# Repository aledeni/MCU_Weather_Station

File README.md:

# MCU Weather Station

The heart of the board is the ATmega328P microcontroller, it also features a 6-pin AVR-ISP connector for burning the bootloader and a USB connector with serial driver for programming the microcontroller. For connectivity, an ESP8266 Wi-Fi module is provided, connected to the ATmega328P.
The boards were ordered from China via the JLCPCB website (5 pcs at a cost of 31 EUR) and the components will be assembled and soldered by myself.
The board schematic can be found in schematic/MCU_Weather_Station.pdf from this git repository.

__Why this board?__

The purpose of the board is to provide a simple but practical example of an online weather station that will use the api.open-meteo.com server for web requests, weather information such as temperature, humidity and time zone will be shown on the OLED display. I will develop the firmware using Arduino IDE.

__PCB view:__

__3D view:__

__Components:__

- 1x ATmega328P DIP-28
- 1x CH340C serial driver SMD
- 1x ESP8266 Olimex_MOD-WIFI-ESP8266-DEV module
- 1x OLED 128x64 SSD1306 display
- 1x AMS1117 voltage regulator (from 5V to 3.3V)
- 1x USB-B THT connector
- 1x DC Barrel Jack 5V THT
- 1x 16 MHz crystal
- 1x 5mm blue LED
- 1x 5mm green LED
- 1x SMD red power LED
- 2x 6mm THT push buttons
- 1x 2x3 AVR-ISP header
- 7x Resistors THT (3x 220Ω | 2x 10kΩ | 1x 1kΩ | 1x 2kΩ)
- 8x 100nF (0.1uF) ceramic capacitors THT
- 2x 22pF ceramic capacitors THT
- 3x 10uF electrolytic radial capacitors THT

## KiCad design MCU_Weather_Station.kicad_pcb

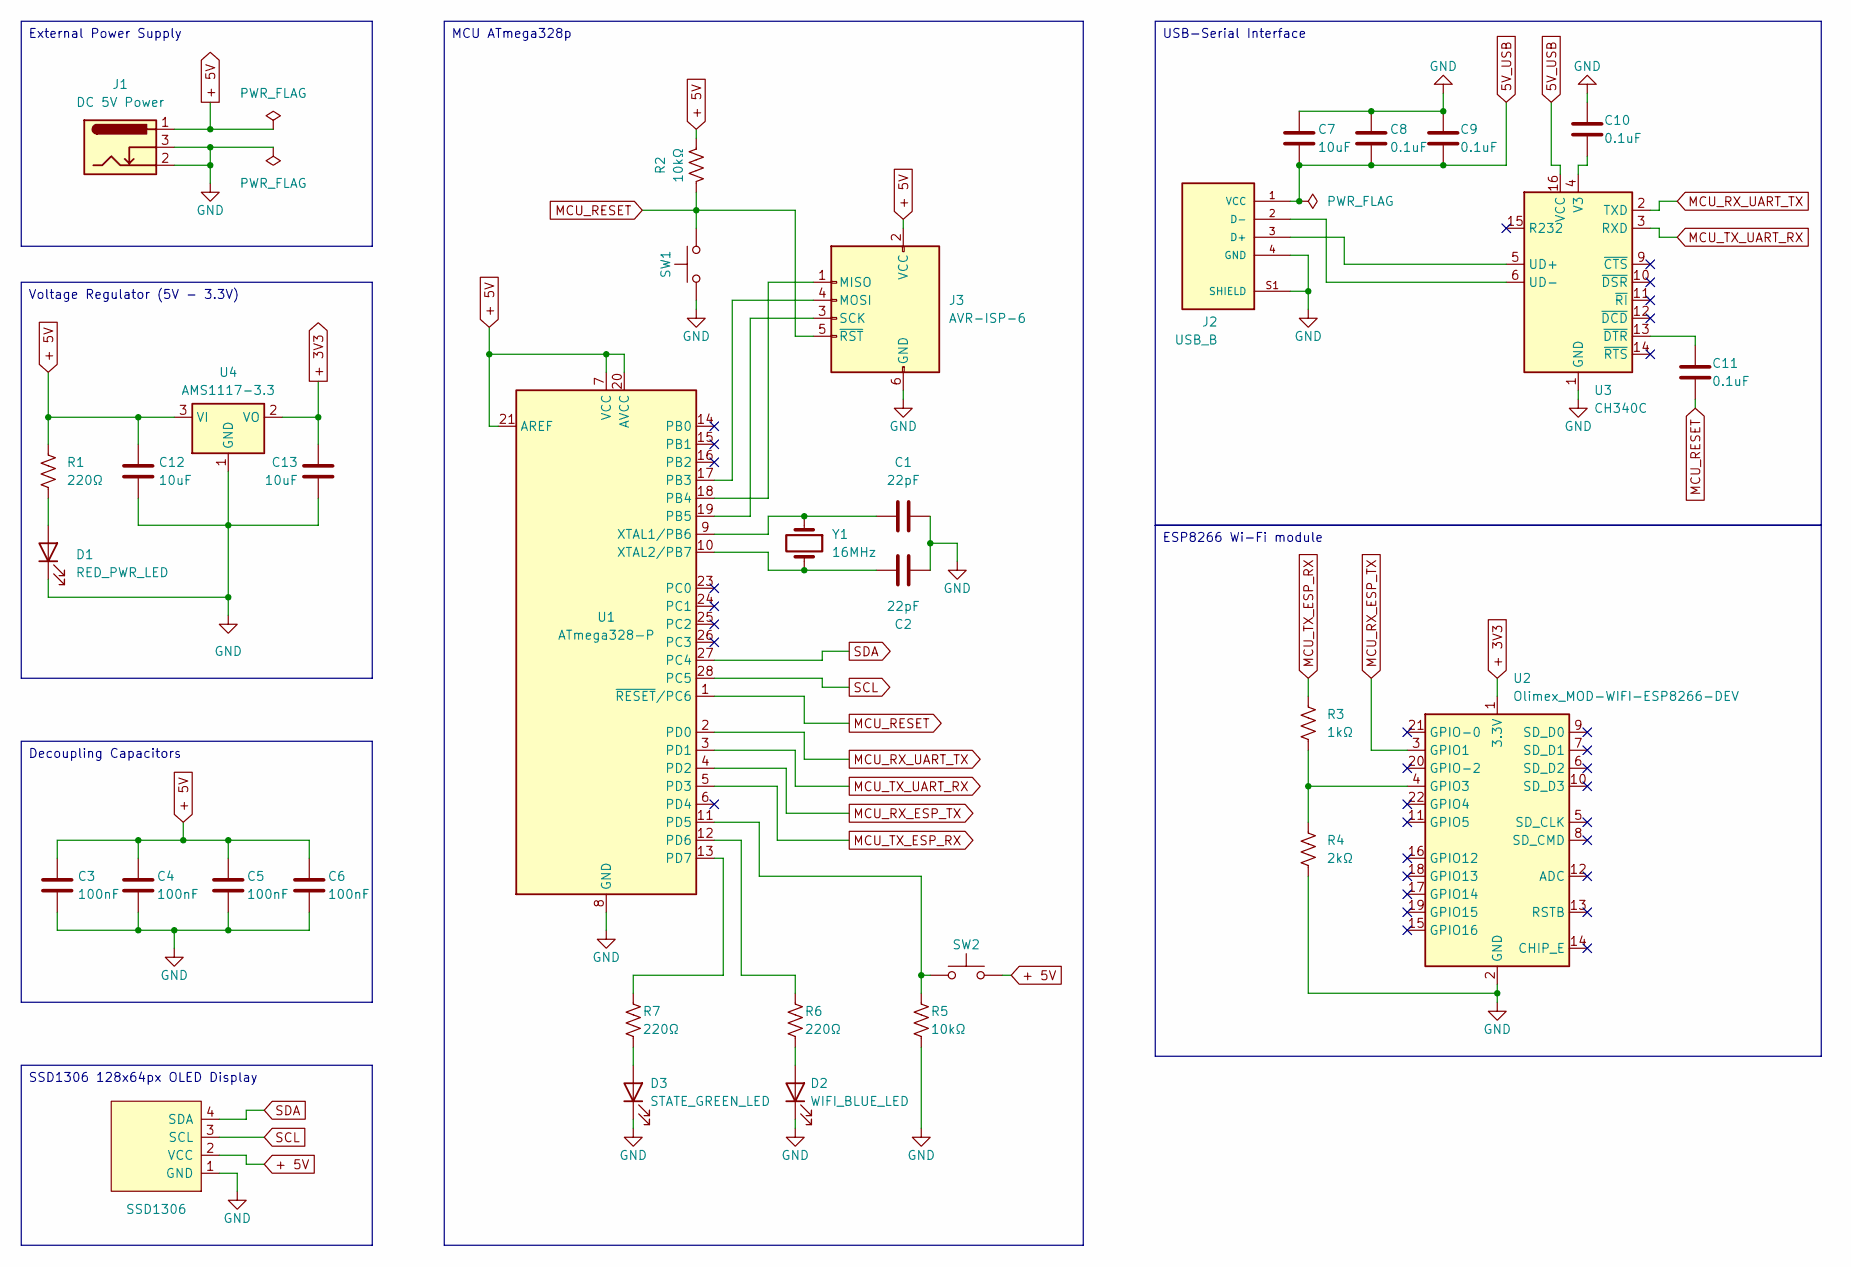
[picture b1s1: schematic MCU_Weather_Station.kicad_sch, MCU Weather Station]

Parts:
Brd1: SSD1306; 128x64OLED
C1, C2: 22pF; C_Disc_D3.0mm_W2.0mm_P2.50mm
C3, C4, C5, C6: 100nF; C_Disc_D5.0mm_W2.5mm_P5.00mm
C7, C12, C13: 10uF; CP_Radial_D5.0mm_P2.00mm
C8, C9, C10, C11: 0.1uF; C_Disc_D5.0mm_W2.5mm_P5.00mm
D1: RED_PWR_LED; LED_1206_3216Metric
D2: WIFI_BLUE_LED; LED_D5.0mm
D3: STATE_GREEN_LED; LED_D5.0mm
J1: DC 5V Power; BarrelJack_Horizontal
J2: USB_B; SAMTEC_USB-B-S-X-X-TH; PARTREV Q
J3: AVR-ISP-6; PinHeader_2x03_P2.54mm_Vertical
R1, R6, R7: 220Ω; R_Axial_DIN0207_L6.3mm_D2.5mm_P7.62mm_Horizontal
R2, R5: 10kΩ; R_Axial_DIN0207_L6.3mm_D2.5mm_P7.62mm_Horizontal
R3: 1kΩ; R_Axial_DIN0207_L6.3mm_D2.5mm_P7.62mm_Horizontal
R4: 2kΩ; R_Axial_DIN0207_L6.3mm_D2.5mm_P7.62mm_Horizontal
SW1: MCU_RESET_BUTTON; SW_PUSH_6mm
SW2: SW_Push; SW_PUSH_6mm
U1: ATmega328-P; DIP-28_W7.62mm
U2: Olimex_MOD-WIFI-ESP8266-DEV
U3: CH340C; SOIC-16_3.9x9.9mm_P1.27mm
U4: AMS1117-3.3; SOT-223-3_TabPin2
Y1: 16MHz; Crystal_HC49-4H_Vertical

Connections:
5V_USB: C7.2, C8.2, C9.2, J2.1 (VCC), U3.16 (VCC)
+ 3V3: C13.1, U2.1 (3.3V), U4.2 (VO)
+ 5V: Brd1.2 (VCC), C3.2, C4.2, C5.2, C6.2, C12.1, J1.1, J3.2 (VCC), R1.1, R2.2, SW2.2, U1.7 (VCC), U1.20 (AVCC), U1.21 (AREF), U4.3 (VI)
GND: Brd1.1 (GND), C1.2, C2.2, C3.1, C4.1, C5.1, C6.1, C7.1, C8.1, C9.1, C10.1, C12.2, C13.2, D1.1 (K), D2.1 (K), D3.1 (K), J1.2, J1.3, J2.4 (GND), J2.S1 (SHIELD), J2.S2 (SHIELD), J3.6 (GND), R4.2, R5.1, SW1.1, U1.8 (GND), U1.22 (GND), U2.2 (GND), U3.1 (GND), U4.1 (GND)
MCU_RESET: C11.2, J3.5 (~RST), R2.1, SW1.2, U1.1 (~RESET/PC6)
MCU_RX_ESP_TX: U1.4 (PD2), U2.3 (GPIO1)
MCU_RX_UART_TX: U1.2 (PD0), U3.2 (TXD)
MCU_TX_ESP_RX: R3.1, U1.5 (PD3)
MCU_TX_UART_RX: U1.3 (PD1), U3.3 (RXD)
unnamed: D1.2 (A), R1.2
unnamed: D2.2 (A), R6.1
unnamed: D3.2 (A), R7.1
unnamed: J2.3 (D+), U3.5 (UD+)
unnamed: J2.2 (D-), U3.6 (UD-)
unnamed: J3.1 (MISO), U1.18 (PB4)
unnamed: J3.4 (MOSI), U1.17 (PB3)
unnamed: J3.3 (SCK), U1.19 (PB5)
unnamed: R5.2, SW2.1, U1.11 (PD5)
unnamed: R6.2, U1.12 (PD6)
unnamed: R7.2, U1.13 (PD7)
unnamed: C1.1, U1.9 (XTAL1/PB6), Y1.1
unnamed: C2.1, U1.10 (XTAL2/PB7), Y1.2
unnamed: R3.2, R4.1, U2.4 (GPIO3)
unnamed: C10.2, U3.4 (V3)
unnamed: C11.1, U3.13 (~DTR)
SCL: Brd1.3 (SCL), U1.28 (PC5)
SDA: Brd1.4 (SDA), U1.27 (PC4)

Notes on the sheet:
Decoupling Capacitors
USB-Serial Interface
MCU ATmega328p
SSD1306 128x64px OLED Display
ESP8266 Wi-Fi module
External Power Supply
Voltage Regulator (5V - 3.3V)

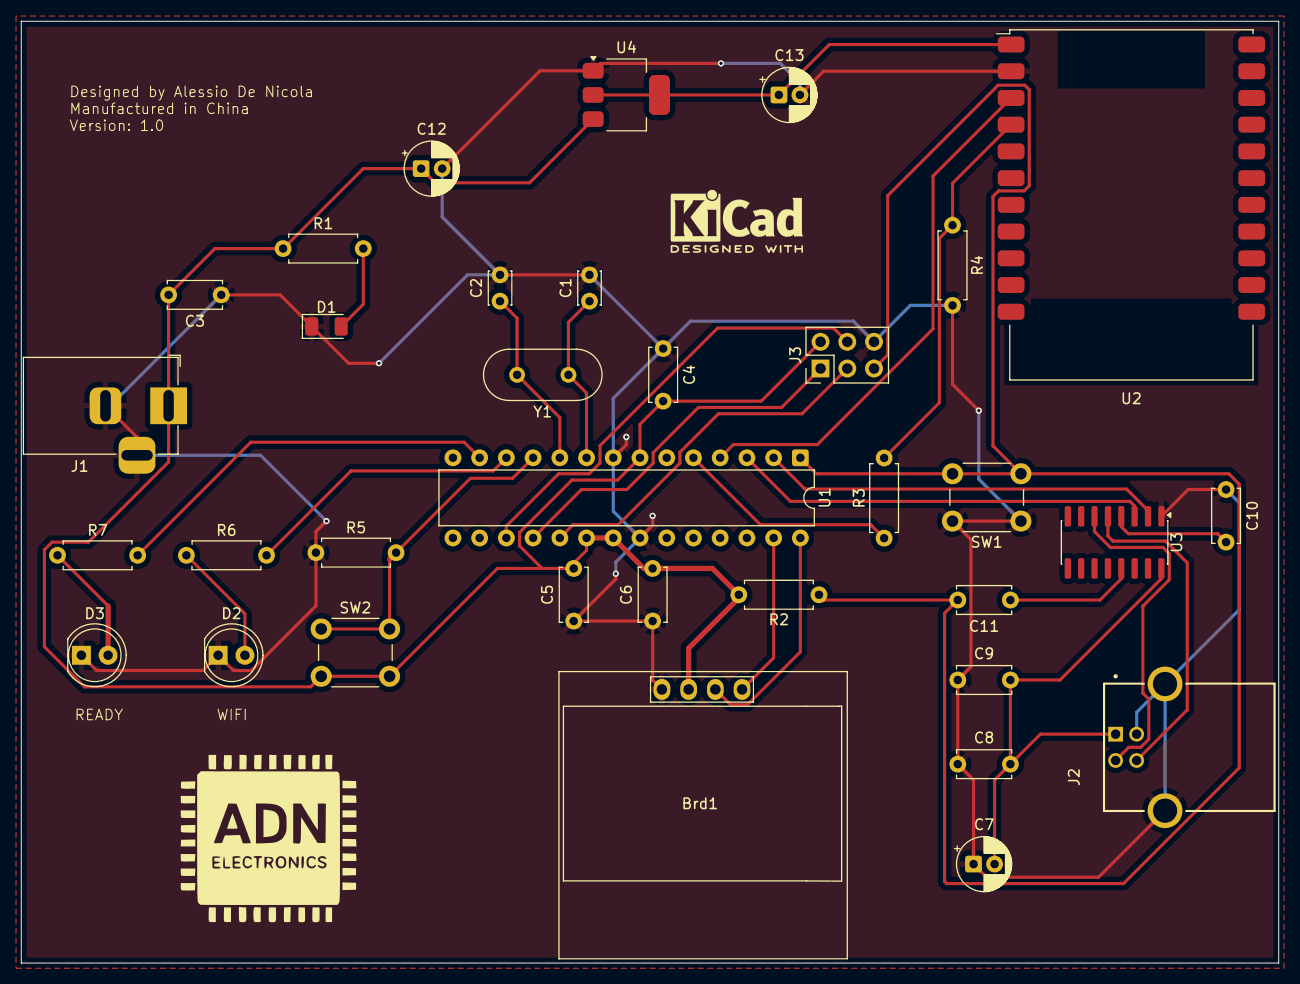
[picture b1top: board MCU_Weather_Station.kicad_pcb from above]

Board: 2 copper layers, 119.5 x 89.5 mm, 34 parts (0 on the bottom side), 27 nets.

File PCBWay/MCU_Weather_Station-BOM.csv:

"Id";"Designator";"Footprint";"Quantity";"Designation";"Supplier and ref";
1;"C6,C3,C5,C4";"C_Disc_D5.0mm_W2.5mm_P5.00mm";4;"100nF";;;
2;"C10,C11,C8,C9";"C_Disc_D5.0mm_W2.5mm_P5.00mm";4;"0.1uF";;;
3;"SW1";"SW_PUSH_6mm";1;"MCU_RESET_BUTTON";;;
4;"J3";"PinHeader_2x03_P2.54mm_Vertical";1;"AVR-ISP-6";;;
5;"D2";"LED_D5.0mm";1;"WIFI_BLUE_LED";;;
6;"U3";"SOIC-16_3.9x9.9mm_P1.27mm";1;"CH340C";;;
7;"R7,R1,R6";"R_Axial_DIN0207_L6.3mm_D2.5mm_P7.62mm_Horizontal";3;"220Ω";;;
8;"C13,C7,C12";"CP_Radial_D5.0mm_P2.00mm";3;"10uF";;;
9;"U2";"Olimex_MOD-WIFI-ESP8266-DEV";1;"Olimex_MOD-WIFI-ESP8266-DEV";;;
10;"R2,R5";"R_Axial_DIN0207_L6.3mm_D2.5mm_P7.62mm_Horizontal";2;"10kΩ";;;
11;"U1";"DIP-28_W7.62mm";1;"ATmega328-P";;;
12;"D3";"LED_D5.0mm";1;"STATE_GREEN_LED";;;
13;"J2";"SAMTEC_USB-B-S-X-X-TH";1;"USB_B";;;
14;"Y1";"Crystal_HC49-4H_Vertical";1;"16MHz";;;
15;"Brd1";"128x64OLED";1;"SSD1306";;;
16;"R3";"R_Axial_DIN0207_L6.3mm_D2.5mm_P7.62mm_Horizontal";1;"1kΩ";;;
17;"C2,C1";"C_Disc_D3.0mm_W2.0mm_P2.50mm";2;"22pF";;;
18;"R4";"R_Axial_DIN0207_L6.3mm_D2.5mm_P7.62mm_Horizontal";1;"2kΩ";;;
19;"SW2";"SW_PUSH_6mm";1;"SW_Push";;;
20;"J1";"BarrelJack_Horizontal";1;"DC 5V Power";;;
21;"D1";"LED_1206_3216Metric";1;"RED_PWR_LED";;;
22;"U4";"SOT-223-3_TabPin2";1;"AMS1117-3.3";;;

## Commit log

2026-02-28 Remove backups folder from tracking
2026-02-28 Add filled zones (GND front and bottom layer) and resolve all DRC errors
2026-02-28 Add PCBWay directory for gerber and BOM files to manufacture
2026-03-01 PCBWay order in state -Subject to audit-
2026-03-02 Pay JLCPCB order
2026-03-03 Add board images and improve README
2026-03-03 Create schematic directory
2026-03-07 Add MIT License to the project
